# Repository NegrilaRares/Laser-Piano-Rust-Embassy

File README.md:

# Laser Piano

## Description

<!-- Describe in a few words your project idea. -->
A piano made using laser diodes and laser receivers.

It uses a potentiometer with leds to adjust and show volume, 3 separete switches with leds to displat change in octave.

The plan is to take the sound data from a microsd card and give it to a dac that will (after going thorough a potentiometer) give the analog output to a speaker.
But there may be a need to amplify the signal in which case i will use a LM386 module from which i will swap the variable resistor with a potentiometer.
## Hardware

<!-- Fill out this table with all the hardware components that you mght need.

The format is 
```
| [Device](link://to/device) | This is used ... | [price](link://to/store) |

```

-->

| Device | Usage | Price |
|--------|--------|-------|
| [Rapspberry Pi Pico W](https://www.raspberrypi.com/documentation/microcontrollers/raspberry-pi-pico.html) | The microcontroller | [35 RON](https://www.optimusdigital.ro/en/raspberry-pi-boards/12394-raspberry-pi-pico-w.html) |
| 13 * Led | This is used for displaying current settings | [-] |
| 13 * 220 Ohm R | This is used to make sure the leds don't get fried | [-] |
| 10 * 10 kOhm R | This is used to create pull up and pull down resistors | [-] |
| 7 * 0.1 uF Capacitor | This is used to debounce the signal from the laser receivers | [-] |
| lots * cables | This is used to connect diffrent things on the breadboard | [-] |
| 10k Potentiometer | This is used for volume input | [2 RON] |
| 2 * [Shift Register]([link://to/device](https://www.diodes.com/assets/Datasheets/74HC595.pdf)) | This is used for the output of the volume setting | [2 RON](https://www.optimusdigital.ro/en/others/2448-registru-de-deplasare-74hc595-dip-16.html) |
| Laser Diode | This is used to generate a laser | [2.5 RON]([link://to/store](https://ardushop.ro/ro/electronica/262-modul-dioda-laser-rou-5mw.html)) |
| 7 * [ISO203]([link://to/device](https://forum.arduino.cc/t/documents-about-laser-sensor-ds18b20/1090450/5)) | This is used to monitor for interference in the path of the laser | [6.5 RON](https://www.optimusdigital.ro/en/others/3289-laser-diode-receiver.html) |
| Catalex MicroSd card slot | This is used to read the data from a microsd | [4.4 RON]([link://to/store](https://www.optimusdigital.ro/en/memories/1516-microsd-card-slot-module.html)) |
| [DAC MCP4725]([link://to/device](https://ww1.microchip.com/downloads/en/devicedoc/22039d.pdf)) | This is used to transfrom the binary from the audio file data into an analog singal for the speaker | [25 RON]([link://to/store](https://www.optimusdigital.ro/en/others/1327-dac-mcp4725-module-with-i2c-interface.html?search_query=dac&results=62)) |
| Speaker | This is used to create a sound based on the analog input given by the system | [-] |
| [AMP LM386]([link://to/device](https://www.ti.com/lit/ds/symlink/lm386.pdf)) | This is used amplify the analog singal | [6.5 RON]([link://to/store](https://ardushop.ro/ro/electronica/241-modul-amplificator-audio-lm386.html)) |

## Hardware Design (work in progress)
[kicad] In the Project-KiCad Folder

## Links

<!-- Add a few links that got you the idea and that you think you will use for your project -->

1. [MicroSd Crate](https://github.com/rust-embedded-community/embedded-sdmmc-rs)
2. [link](https://example3.com)
...

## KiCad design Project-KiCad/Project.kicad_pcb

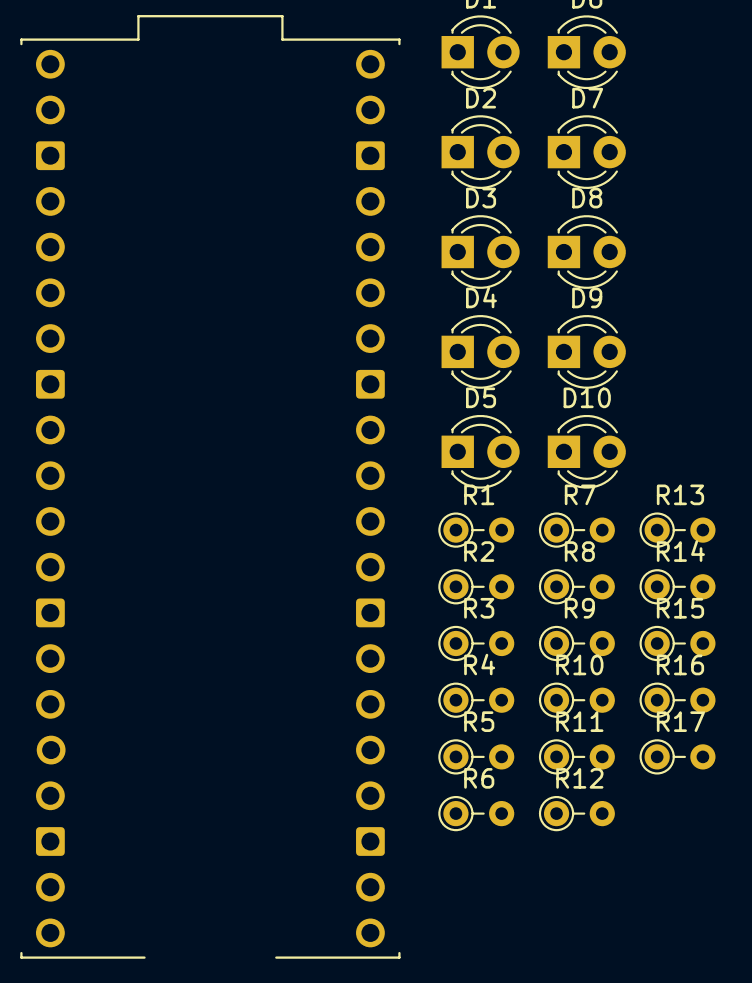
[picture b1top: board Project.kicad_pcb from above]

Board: 2 copper layers, 28 parts (0 on the bottom side), 18 nets, no tracks yet.

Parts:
A1: SC0918; MODULE_SC0918
D1, D2, D3, D4, D5, D6, D7, D8, D9, D10: LED; LED_D3.0mm
R1, R2, R3, R4, R5, R6, R7, R8, R9, R10, R11, R12, R13, R14, R15, R16, R17: R; R_Axial_DIN0204_L3.6mm_D1.6mm_P2.54mm_Vertical

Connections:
unnamed: A1.1 (GP0), R11.2
unnamed: A1.2 (GP1), R12.2
unnamed: A1.4 (GP2), R13.2
unnamed: A1.5 (GP3), R14.2
unnamed: A1.6 (GP4), R15.2
unnamed: A1.7 (GP5), R16.2
unnamed: A1.9 (GP6), R17.2
unnamed: D1.2 (A), R1.2
unnamed: A1.38 (GND), D1.1 (K), D2.1 (K), D3.1 (K), D4.1 (K), D5.1 (K), D6.1 (K), D7.1 (K), D8.1 (K), D9.1 (K), D10.1 (K)
unnamed: D2.2 (A), R2.1
unnamed: D3.2 (A), R3.2
unnamed: D4.2 (A), R4.2
unnamed: D5.2 (A), R5.1
unnamed: D6.2 (A), R6.2
unnamed: D7.2 (A), R7.2
unnamed: D8.2 (A), R8.2
unnamed: D9.2 (A), R9.2
unnamed: D10.2 (A), R10.2

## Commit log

2024-04-22 upload progress
2025-03-17 Rename index.md to README.md
